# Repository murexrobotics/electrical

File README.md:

# MUREX Electrical

Attempt the impossible.

## Welcome!

Welcome to MUREX Robotics Electrical. We are focused on pushing boundaries and making electronics/systems design more accessible to all.

## Introduction

> *"I do not think there is any thrill that can go through the human heart like that felt by the inventor as he sees some creation of the brain unfolding to success"*
– [Nikola Tesla](https://en.wikipedia.org/wiki/Nikola_Tesla)

MUREX Robotics Electrical focuses on making everything highly integrated and custom. We make industrial/commercial level motion, power, communication, vision and wireless systems accessible to all. By making components fully custom, we can accomplish unprecedented levels of integration within MUREX robotics systems. By keeping COTS parts to a minimum, we vertically integrate all aspects of the robot, minimize space, and surprisingly, minimize cost. We don't do it the easy way. That's not what we believe in.

## Attempt the Impossible

Going to back our "mission statement"... (it's not really a mission statement, more a motivational quote)

> *Attempt the impossible*

What does this mean? Now that you have read through what MUREX Robotics Electrical (or *elec*) is all about and equipped with technical expertise, we can finally say what the true meaning is.

***Attempt the impossible***: We do it the best way possible. If pre-built parts or breakout boards don't cut it, we don't use it. If a processor isn't powerful enough, we don't use it. If a board isn't small enough, we make it smaller. No matter how difficult it may be to accomplish, we will follow through. No matter how hard it is. Things don't always go your way. No matter how hard you try to perfect your schematic, your PCB layout, your system integration, it still might not work out. Things are bound to go wrong, and it is up to *us* do it right. It's "impossible", a non-MUREX Robotics Electrical member might say. However, we accept it as the process. In the end, we will have achieved something others might have called "impossible". But the achievement only comes through endless, motivated attempts at the impossible.

> *Think Different*\
> *Unleash Innovation*\
> *Do It Right*

*Always attempting the impossible,*\
Members:

- Max Liu '26 (@xamuil2)
- Crane Lee '27 (@Crane-Lee)
- Osbert Chang '27 (@Osbertchang)
- Andrew Chen '28

Emeriti:

- Byran Huang '25 (@Hello9999901)
- Altan Unver '25 (@L0ad1n6)
- Varit Asavathiratham '25 (@BaritoDespacito)
- Chaney Hollis '23 (@chaneyhollis)

> December 2023 progress poster

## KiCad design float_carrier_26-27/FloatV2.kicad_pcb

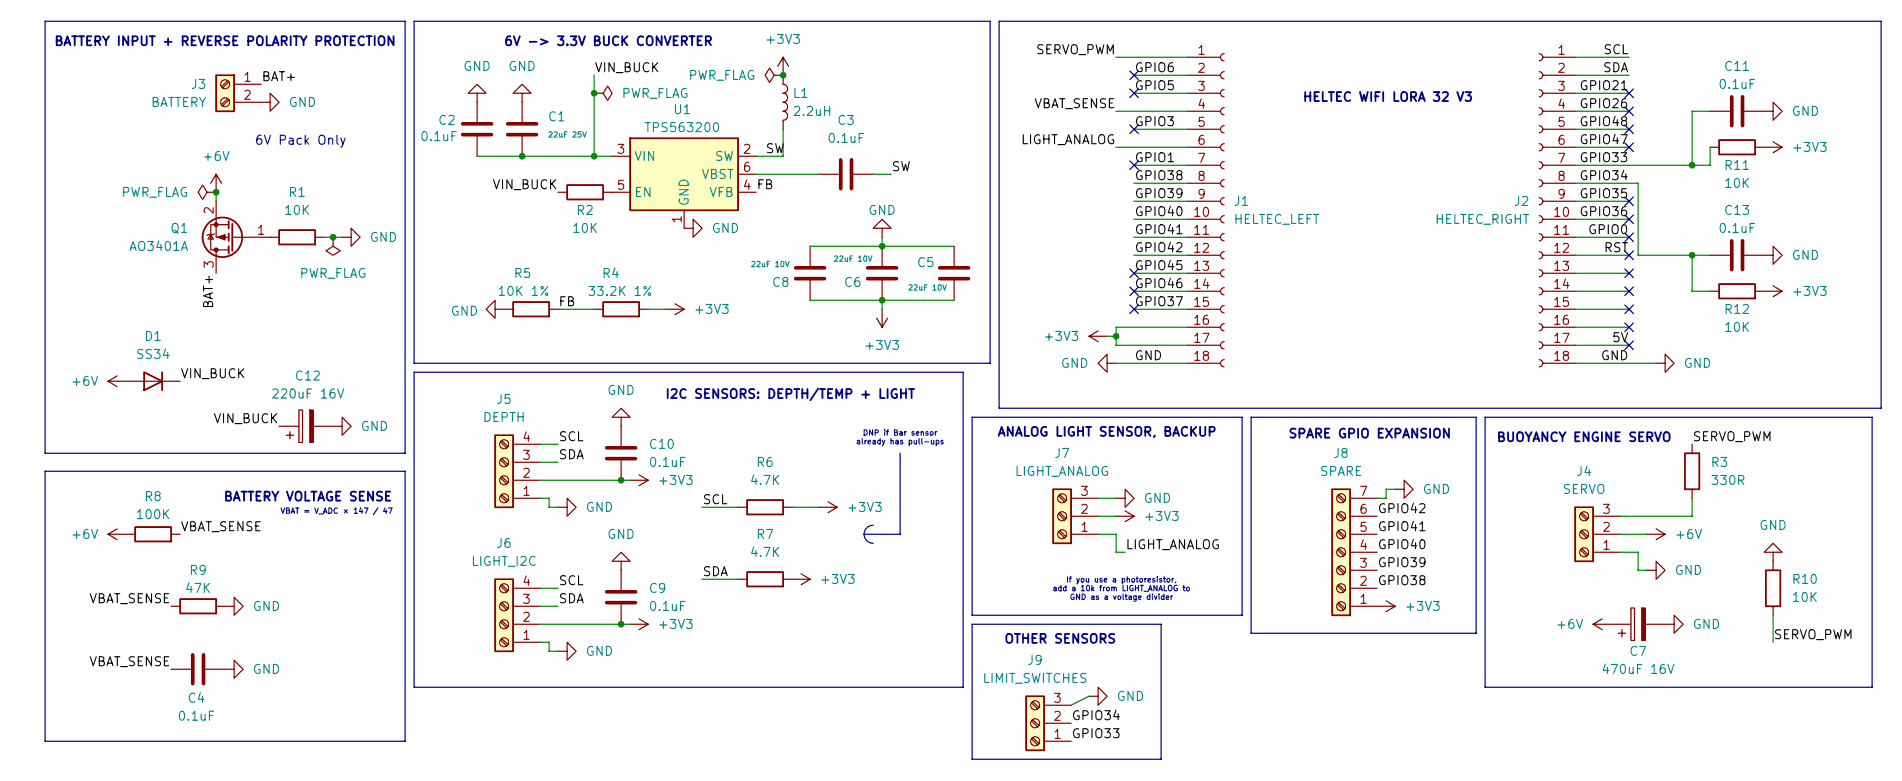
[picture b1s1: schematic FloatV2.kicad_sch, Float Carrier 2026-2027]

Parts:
C1: 22uF 25V; C_1206_3216Metric
C2, C3, C4, C9, C10, C11, C13: 0.1uF; C_0603_1608Metric
C5, C6, C8: 22uF 10V; C_0805_2012Metric
C7: 470uF 16V; CP_Elec_8x10
C12: 220uF 16V; CP_Elec_8x10
D1: SS34; D_SMA
J1: HELTEC_LEFT; PinSocket_1x18_P2.54mm_Vertical
J2: HELTEC_RIGHT; PinSocket_1x18_P2.54mm_Vertical
J3: BATTERY; TerminalBlock_Xinya_XY308-2.54-2P_1x02_P2.54mm_Horizontal
J4: SERVO; TerminalBlock_Xinya_XY308-2.54-3P_1x03_P2.54mm_Horizontal
J5: DEPTH; TerminalBlock_Xinya_XY308-2.54-4P_1x04_P2.54mm_Horizontal
J6: LIGHT_I2C; TerminalBlock_Xinya_XY308-2.54-4P_1x04_P2.54mm_Horizontal
J7: LIGHT_ANALOG; TerminalBlock_Xinya_XY308-2.54-3P_1x03_P2.54mm_Horizontal
J8: SPARE; TerminalBlock_Xinya_XY308-2.54-7P_1x07_P2.54mm_Horizontal
J9: LIMIT_SWITCHES; TerminalBlock_Xinya_XY308-2.54-3P_1x03_P2.54mm_Horizontal
L1: 2.2uH; L_Bourns_SRP7028A_7.3x6.6mm
Q1: AO3401A; SOT-23
R1, R2, R10, R11, R12: 10K; R_0603_1608Metric
R3: 330R; R_0603_1608Metric
R4: 33.2K 1%; R_0603_1608Metric
R5: 10K 1%; R_0603_1608Metric
R6, R7: 4.7K; R_0603_1608Metric
R8: 100K; R_0603_1608Metric
R9: 47K; R_0603_1608Metric
U1: TPS563200; SOT-23-6

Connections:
+3V3: C5.2, C6.1, C8.1, C9.2, C10.2, J1.16, J1.17, J5.2, J6.2, J7.2, J8.1, L1.1, R4.2, R6.2, R7.2, R11.2, R12.2
+6V: C7.1, D1.2 (A), J4.2, Q1.2 (S), R8.1
/5V: J2.17
/BAT+: J3.1, Q1.3 (D)
/FB: R4.1, R5.2, U1.4 (VFB)
/GPIO0: J2.11
/GPIO1: J1.7
/GPIO3: J1.5
/GPIO5: J1.3
/GPIO6: J1.2
/GPIO21: J2.3
/GPIO26: J2.4
/GPIO33: C11.1, J2.7, J9.1, R11.1
/GPIO34: C13.1, J2.8, J9.2, R12.1
/GPIO35: J2.9
/GPIO36: J2.10
/GPIO37: J1.15
/GPIO38: J1.8, J8.2
/GPIO39: J1.9, J8.3
/GPIO40: J1.10, J8.4
/GPIO41: J1.11, J8.5
/GPIO42: J1.12, J8.6
/GPIO45: J1.13
/GPIO46: J1.14
/GPIO47: J2.6
/GPIO48: J2.5
/LIGHT_ANALOG: J1.6, J7.1
/RST: J2.12
/SCL: J2.1, J5.4, J6.4, R6.1
/SDA: J2.2, J5.3, J6.3, R7.1
/SERVO_PWM: J1.1, R3.1, R10.2
/SW: C3.1, L1.2, U1.2 (SW)
/VBAT_SENSE: C4.2, J1.4, R8.2, R9.1
/VIN_BUCK: C1.2, C2.2, C12.1, D1.1 (K), R2.1, U1.3 (VIN)
GND: C1.1, C2.1, C4.1, C5.1, C6.2, C7.2, C8.2, C9.1, C10.1, C11.2, C12.2, C13.2, J1.18, J2.18, J3.2, J4.1, J5.1, J6.1, J7.3, J8.7, J9.3, R1.2, R5.1, R9.2, R10.1, U1.1 (GND)
unnamed: J4.3, R3.2
unnamed: Q1.1 (G), R1.1
unnamed: R2.2, U1.5 (EN)
unnamed: C3.2, U1.6 (VBST)

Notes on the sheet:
I2C SENSORS: DEPTH/TEMP + LIGHT
BATTERY INPUT + REVERSE POLARITY PROTECTION
6V Pack Only
SPARE GPIO EXPANSION
6V -> 3.3V BUCK CONVERTER
VBAT = V_ADC × 147 / 47
DNP if Bar sensor already has pull-ups
HELTEC WIFI LORA 32 V3
ANALOG LIGHT SENSOR, BACKUP
If you use a photoresistor, add a 10k from LIGHT_ANALOG to GND as a voltage divider
BATTERY VOLTAGE SENSE
OTHER SENSORS
BUOYANCY ENGINE SERVO

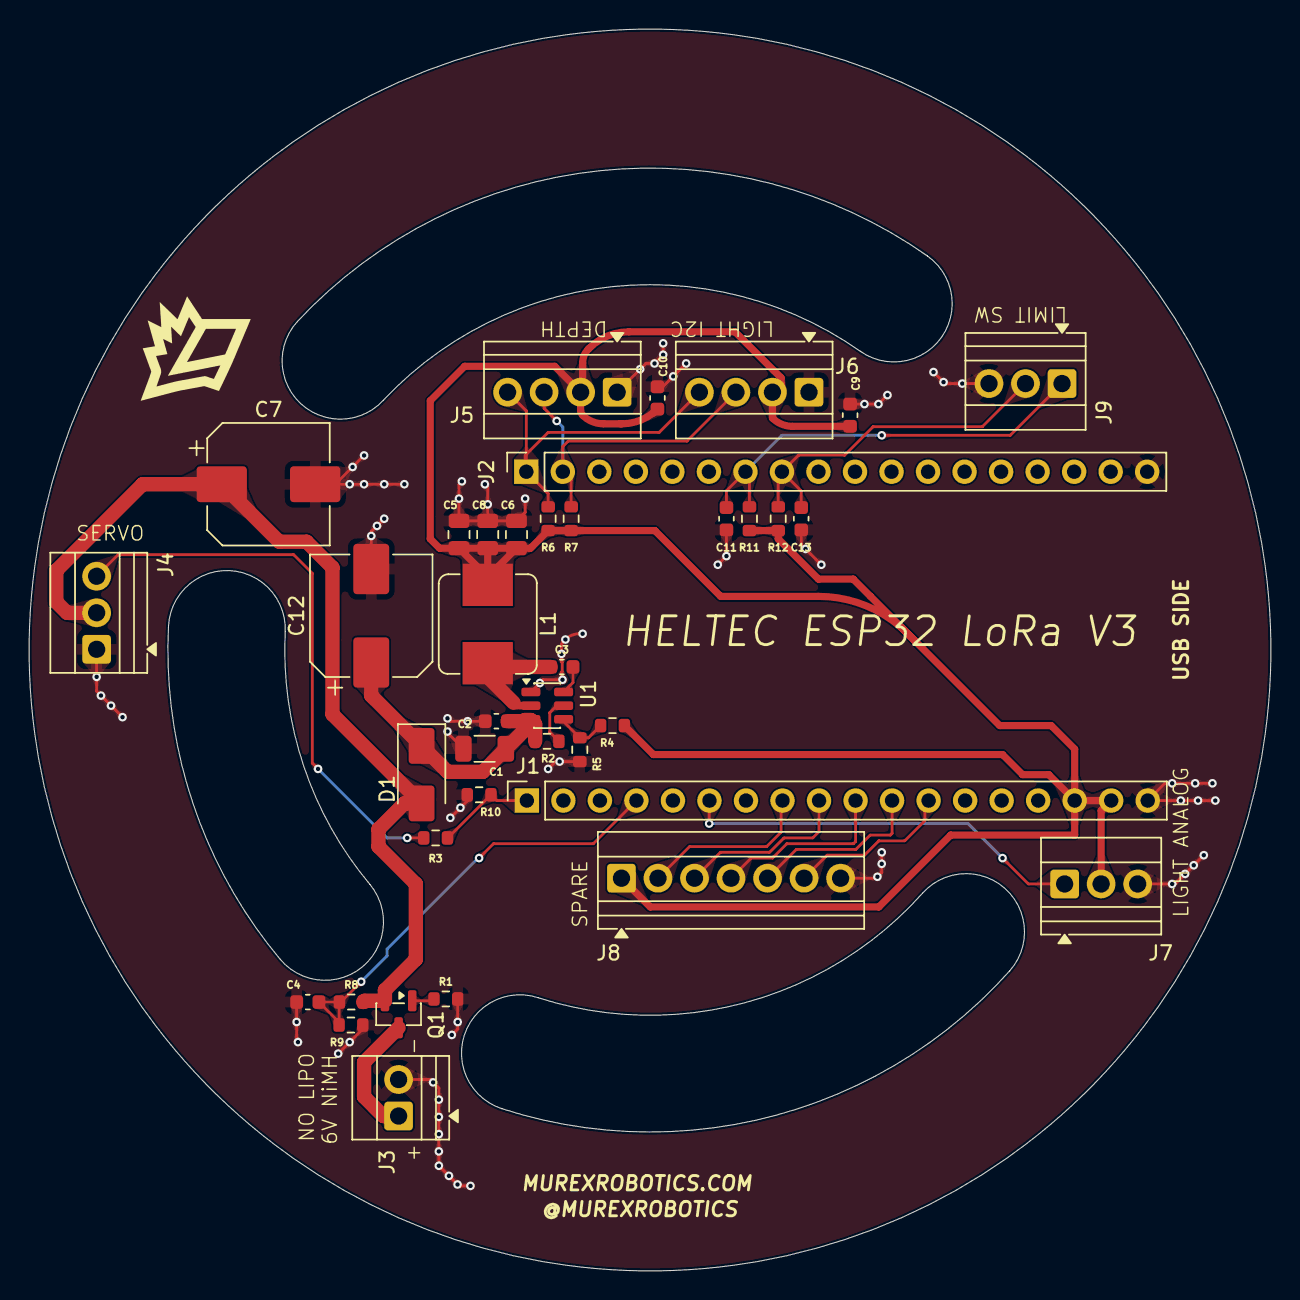
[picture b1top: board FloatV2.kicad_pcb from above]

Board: 4 copper layers, 86.4 x 86.4 mm, 38 parts (0 on the bottom side), 23 nets.

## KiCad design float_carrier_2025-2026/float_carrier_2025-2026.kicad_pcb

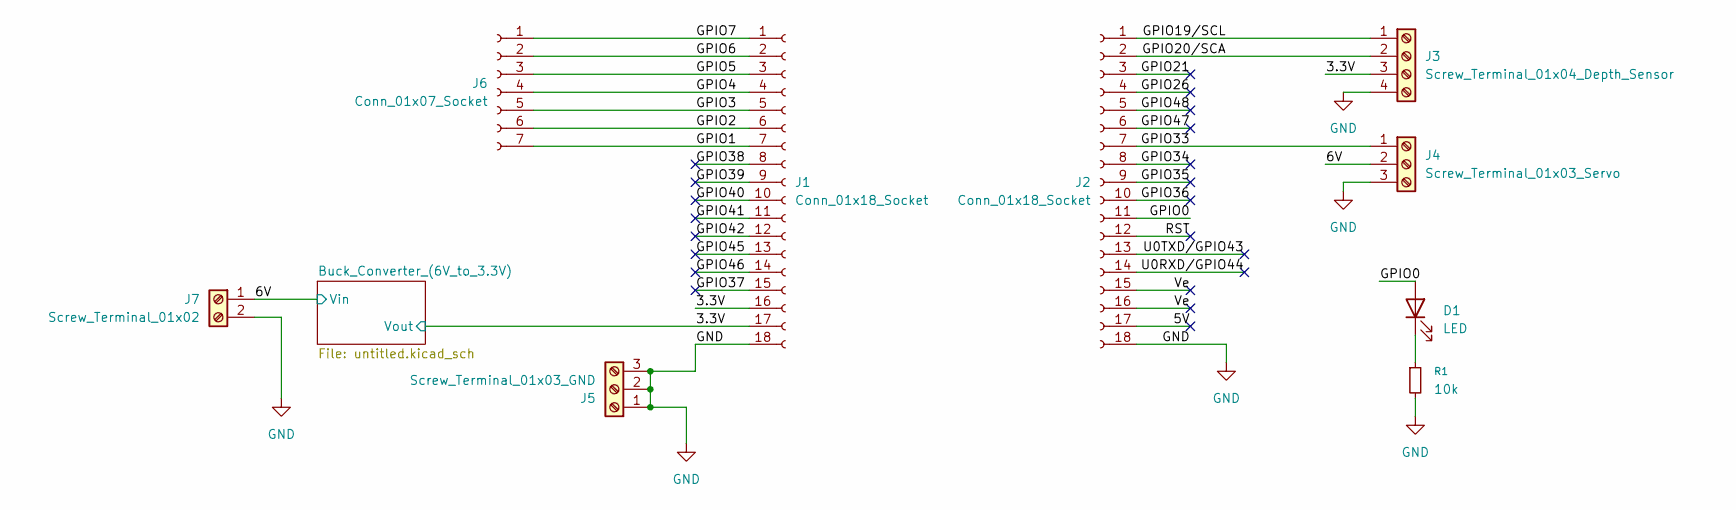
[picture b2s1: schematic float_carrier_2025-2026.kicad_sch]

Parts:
D1: LED; LED_0603_1608Metric
J1, J2: Conn_01x18_Socket; PinSocket_1x18_P2.54mm_Vertical
J3: Screw_Terminal_01x04_Depth_Sensor; TerminalBlock_Xinya_XY308-2.54-4P_1x04_P2.54mm_Horizontal
J4: Screw_Terminal_01x03_Servo; TerminalBlock_Xinya_XY308-2.54-3P_1x03_P2.54mm_Horizontal
J5: Screw_Terminal_01x03_GND; TerminalBlock_Xinya_XY308-2.54-3P_1x03_P2.54mm_Horizontal
J6: Conn_01x07_Socket; PinSocket_1x07_P2.54mm_Vertical
J7: Screw_Terminal_01x02; TerminalBlock_Xinya_XY308-2.54-2P_1x02_P2.54mm_Horizontal
R1: 10k; R_0603_1608Metric

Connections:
/3.3V: J1.16, J1.17, J3.3; also elsewhere on the board
/5V: J2.17
/6V: J4.2, J7.1; also elsewhere on the board
/GPIO0: D1.2 (A), J2.11
/GPIO1: J1.7, J6.7
/GPIO2: J1.6, J6.6
/GPIO3: J1.5, J6.5
/GPIO4: J1.4, J6.4
/GPIO5: J1.3, J6.3
/GPIO6: J1.2, J6.2
/GPIO7: J1.1, J6.1
/GPIO19/SCL: J2.1, J3.1
/GPIO20/SCA: J2.2, J3.2
/GPIO21: J2.3
/GPIO26: J2.4
/GPIO33: J2.7, J4.1
/GPIO34: J2.8
/GPIO35: J2.9
/GPIO36: J2.10
/GPIO37: J1.15
/GPIO38: J1.8
/GPIO39: J1.9
/GPIO40: J1.10
/GPIO41: J1.11
/GPIO42: J1.12
/GPIO45: J1.13
/GPIO46: J1.14
/GPIO47: J2.6
/GPIO48: J2.5
/RST: J2.12
/U0RXD/GPIO44: J2.14
/U0TXD/GPIO43: J2.13
/Ve: J2.15, J2.16
GND: J1.18, J2.18, J3.4, J4.3, J5.1, J5.2, J5.3, J7.2, R1.2; also elsewhere on the board
unnamed: D1.1 (K), R1.1

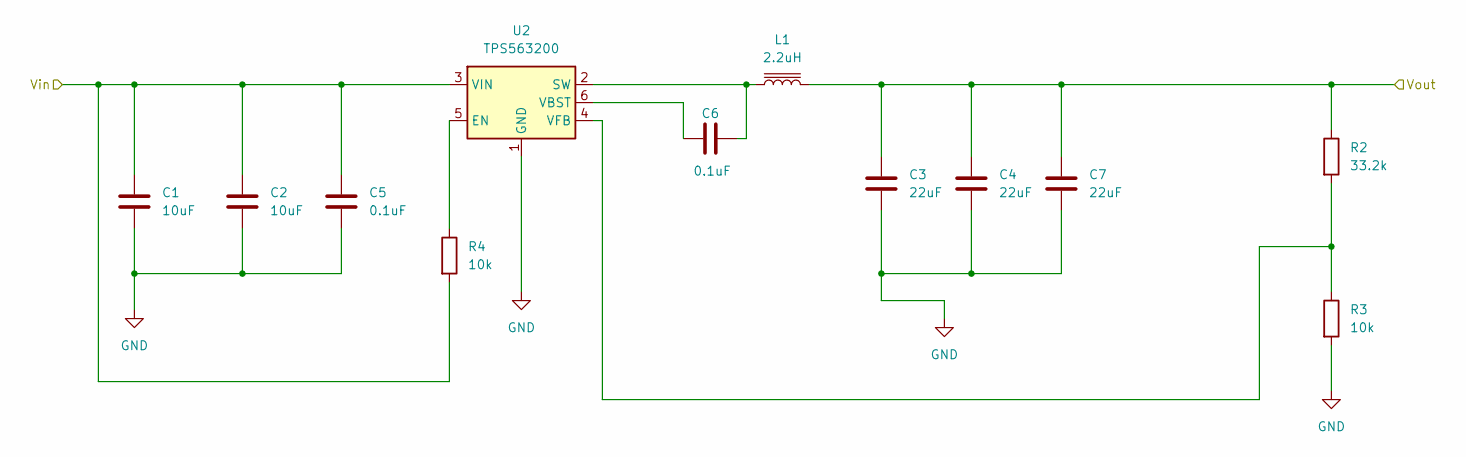
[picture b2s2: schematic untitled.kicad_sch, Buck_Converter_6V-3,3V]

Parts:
C1, C2: 10uF; C_0603_1608Metric
C3, C4, C7: 22uF; C_0603_1608Metric
C5, C6: 0.1uF; C_0402_1005Metric
L1: 2.2uH; L_Bourns_SRP7028A_7.3x6.6mm
R2: 33.2k; R_0603_1608Metric
R3, R4: 10k; R_0603_1608Metric
U2: TPS563200; SOT-23-6

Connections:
/3.3V: C3.1, C4.1, C7.1, L1.2, R2.1; also elsewhere on the board
/6V: C1.1, C2.1, C5.1, R4.2, U2.3 (VIN); also elsewhere on the board
GND: C1.2, C2.2, C3.2, C4.2, C5.2, C7.2, R3.2, U2.1 (GND); also elsewhere on the board
unnamed: R4.1, U2.5 (EN)
unnamed: C6.2, L1.1, U2.2 (SW)
unnamed: C6.1, U2.6 (VBST)
unnamed: R2.2, R3.1, U2.4 (VFB)

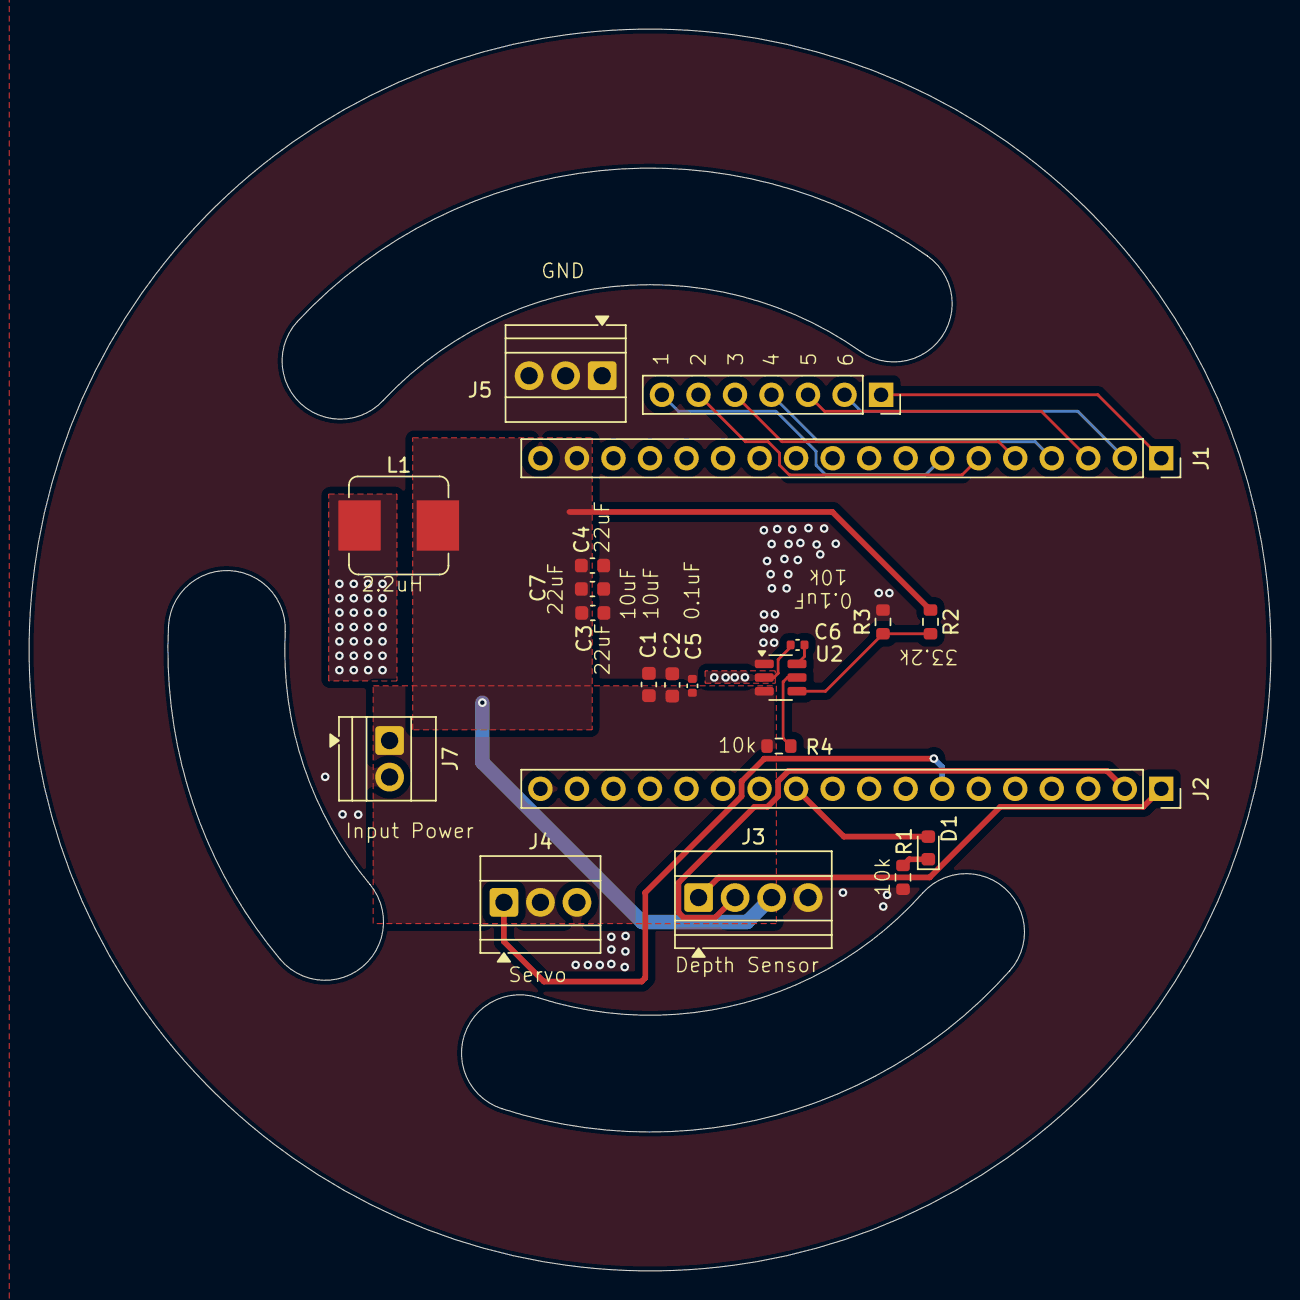
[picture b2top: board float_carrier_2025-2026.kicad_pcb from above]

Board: 2 copper layers, 86.4 x 86.4 mm, 21 parts (0 on the bottom side), 20 nets.

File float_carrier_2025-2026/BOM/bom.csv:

Comment,Designator,Footprint,LSCS Part Number
0.1uF,"C5, C6",C_0402_1005Metric,C141382
10uF,"C1, C2",C_0603_1608Metric,C694533
22uF,"C3, C4, C7",C_0603_1608Metric,C60077
LED,D1,LED_0603_1608Metric,C2286
2.2uH,L1,L_Bourns_SRP7028A_7.3x6.6mm,C2847539
10k,"R1, R3, R4",R_0603_1608Metric,C5123581
33.2k,R2,R_0603_1608Metric,C23003
TPS563200,U2,SOT-23-6,C97253

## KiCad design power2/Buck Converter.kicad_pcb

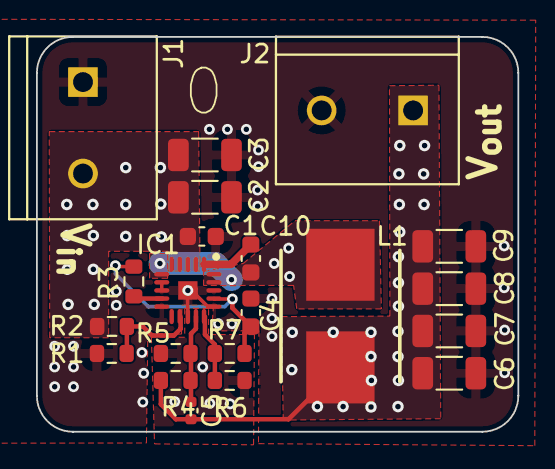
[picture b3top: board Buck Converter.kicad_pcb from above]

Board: 4 copper layers, 26.7 x 21.9 mm, 21 parts (0 on the bottom side), 10 nets.

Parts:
C1, C10: 0.1uF; C_0603_1608Metric
C2, C3: 22uF; C_1206_3216Metric
C4: 1uF; C_0603_1608Metric
C5: 68pF; C_0402_1005Metric
C6, C7, C8, C9: 47uF; C_1206_3216Metric
IC1: TPS56C230RJER; QFN45P300X300X100-21N-D
J1, J2: TE_282837-2
L1: SRP7028A-1R8M; INDPM7366X300N
R1: 51k; R_0603_1608Metric
R2: 102k; R_0603_1608Metric
R3: 100k; R_0603_1608Metric
R4: 110k; R_0603_1608Metric
R5, R6: 15k; R_0603_1608Metric
R7: 330k; R_0603_1608Metric

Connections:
/EN: IC1.12 (EN), R1.1, R2.2
/MODE: IC1.15 (MODE), R6.1, R7.1
/V_{IN}: C1.2, C2.2, C3.2, IC1.2 (VIN_1), IC1.3 (VIN_2), IC1.4 (VIN_3), IC1.5 (VIN_4), J1.2, R2.1
/V_{OUT}: C5.2, C6.1, C7.1, C8.1, C9.1, J2.1, L1.2, R4.1
GND: C1.1, C2.1, C3.1, C4.2, C6.2, C7.2, C8.2, C9.2, IC1.7 (PGND_1), IC1.8 (PGND_2), IC1.10 (NC_1), IC1.13 (AGND), IC1.16 (NC_2), IC1.18 (PGND_3), IC1.21 (PGND_4), J1.1, J2.2, R1.2, R5.2, R6.2
unnamed: C10.1, IC1.1 (BST)
unnamed: C5.1, IC1.14 (FB), R4.2, R5.1
unnamed: IC1.9 (PGOOD), R3.2
unnamed: C10.2, IC1.6 (SW_1), IC1.19 (SW_2), IC1.20 (SW_3), L1.1
unnamed: C4.1, IC1.17 (VCC), R3.1, R7.2

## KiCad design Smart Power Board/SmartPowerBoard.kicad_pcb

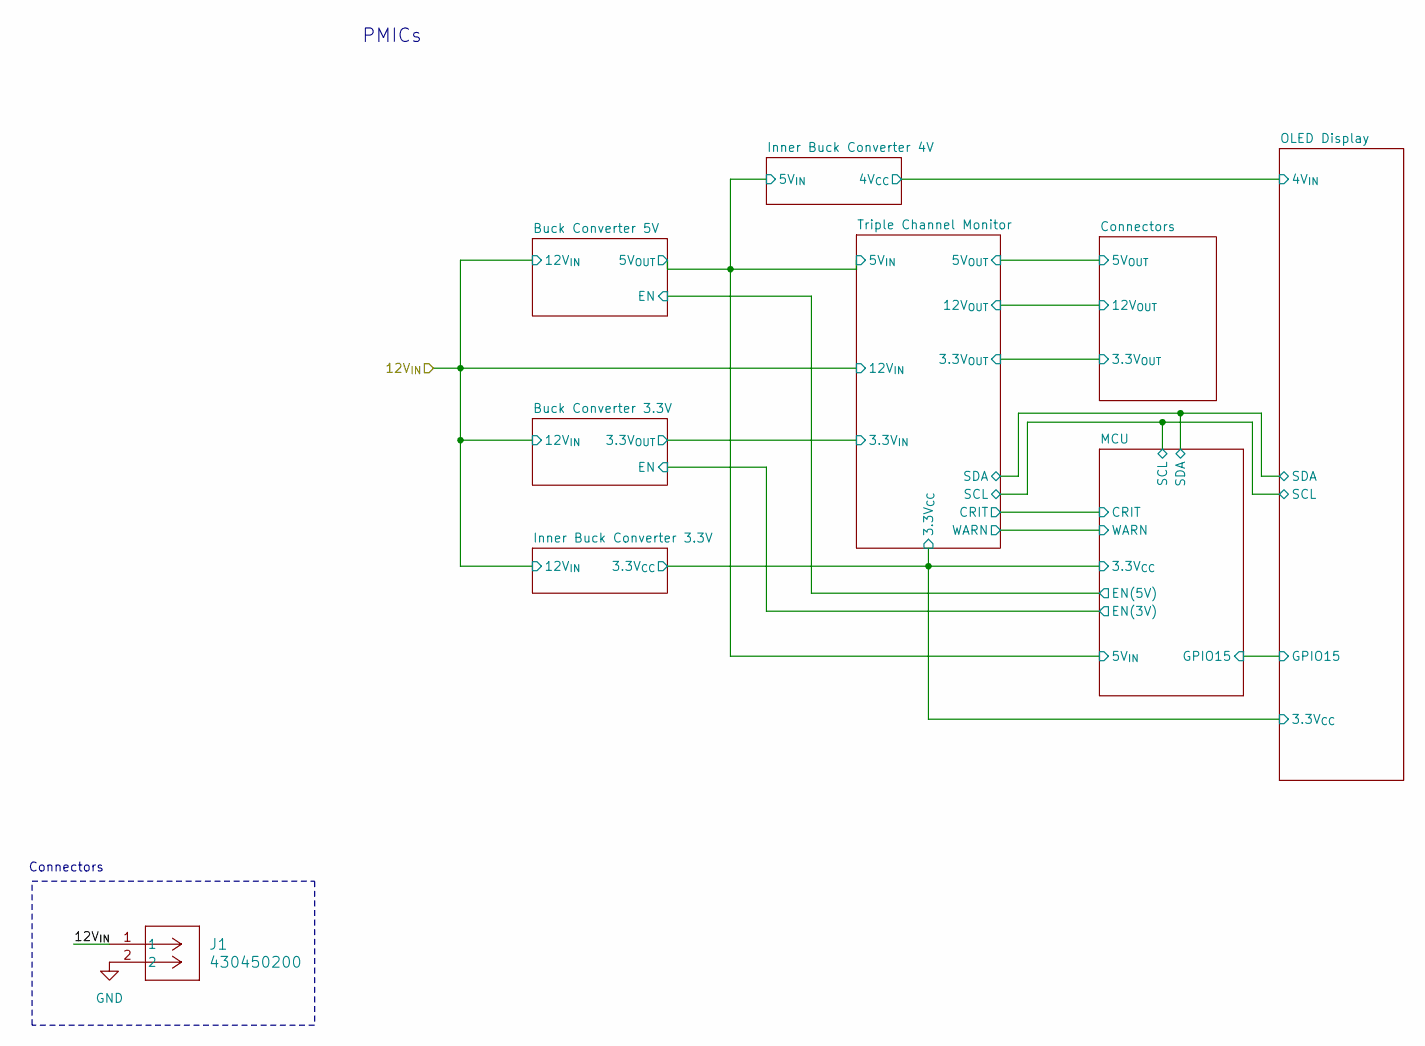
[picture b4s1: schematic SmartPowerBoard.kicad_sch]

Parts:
J1: 430450200; CON_430450200_MOL

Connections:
/12V_{IN}: J1.1; also elsewhere on the board
GND: J1.2; also elsewhere on the board

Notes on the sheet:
Connectors
PMICs

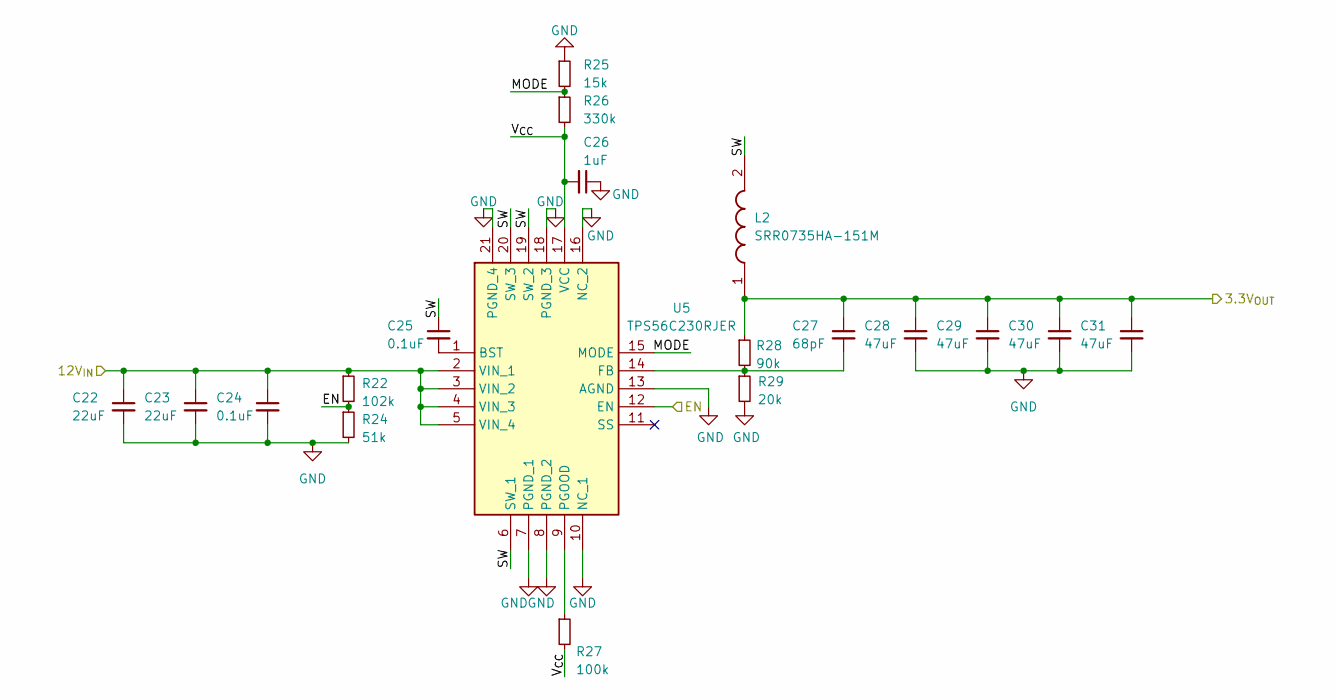
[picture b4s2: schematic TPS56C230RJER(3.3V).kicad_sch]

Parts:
C22, C23: 22uF; C_0603_1608Metric
C24, C25: 0.1uF; C_0402_1005Metric
C26: 1uF; C_0402_1005Metric
C27: 68pF; C_0201_0603Metric
C28, C29, C30, C31: 47uF; C_0603_1608Metric
L2: SRR0735HA-151M; SRR0735HA151M; Mouser Part Number 652-SRR0735HA-151M
R22: 102k; R_0402_1005Metric
R24: 51k; R_0402_1005Metric
R25: 15k; R_0402_1005Metric
R26: 330k; R_0402_1005Metric
R27: 100k; R_0402_1005Metric
R28: 90k; R_0402_1005Metric
R29: 20k; R_0402_1005Metric
U5: TPS56C230RJER; QFN45P300X300X100-21N-D; Manufacturer_Part_Number TPS56C230RJER; Mouser Part Number 595-TPS56C230RJER

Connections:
/12V_{IN}: C22.1, C23.1, C24.1, R22.1, U5.2 (VIN_1), U5.3 (VIN_2), U5.4 (VIN_3), U5.5 (VIN_4); also elsewhere on the board
/Buck Converter 3.3V/3.3V_{OUT}: C27.1, C28.1, C29.1, C30.1, C31.1, L2.1, R28.1; also elsewhere on the board
/Buck Converter 3.3V/EN: R22.2, R24.1, U5.12 (EN); also elsewhere on the board
/Buck Converter 3.3V/MODE: R25.2, R26.1, U5.15 (MODE)
/Buck Converter 3.3V/SW: C25.1, L2.2, U5.6 (SW_1), U5.19 (SW_2), U5.20 (SW_3)
/Buck Converter 3.3V/V_{CC}: C26.2, R26.2, R27.2, U5.17 (VCC)
GND: C22.2, C23.2, C24.2, C26.1, C28.2, C29.2, C30.2, C31.2, R24.2, R25.1, R29.2, U5.7 (PGND_1), U5.8 (PGND_2), U5.10 (NC_1), U5.13 (AGND), U5.16 (NC_2), U5.18 (PGND_3), U5.21 (PGND_4); also elsewhere on the board
unnamed: C25.2, U5.1 (BST)
unnamed: C27.2, R28.2, R29.1, U5.14 (FB)
unnamed: R27.1, U5.9 (PGOOD)

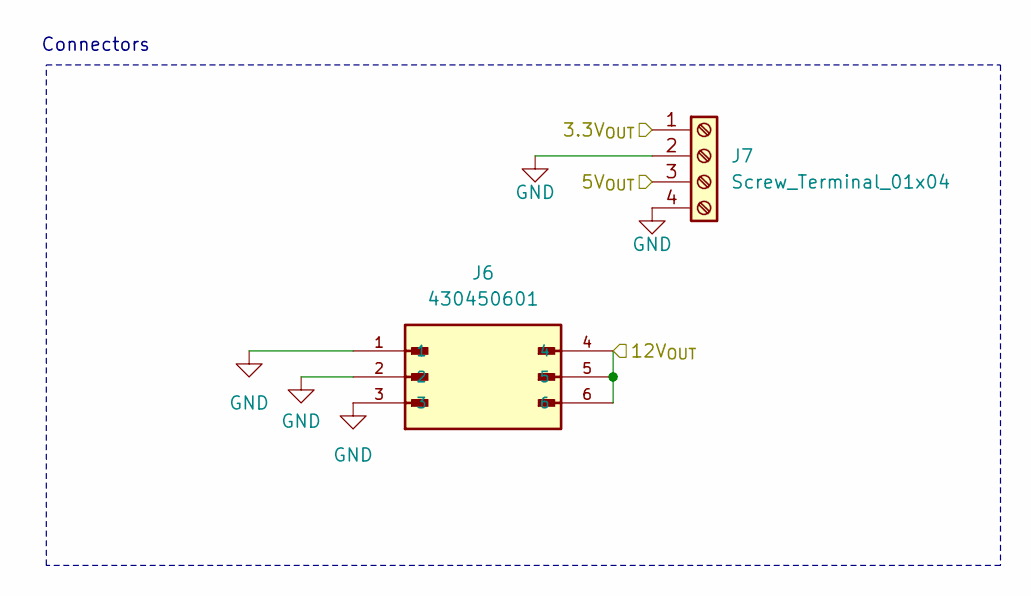
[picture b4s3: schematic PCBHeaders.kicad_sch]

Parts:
J6: 430450601; MOLEX_430450601; PARTREV G
J7: Screw_Terminal_01x04; 2828574

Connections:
/Connectors/3.3V_{OUT}: J7.1; also elsewhere on the board
/Connectors/5V_{OUT}: J7.3; also elsewhere on the board
/Connectors/12V_{OUT}: J6.4, J6.5, J6.6; also elsewhere on the board
GND: J6.1, J6.2, J6.3, J7.2, J7.4; also elsewhere on the board

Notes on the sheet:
Connectors

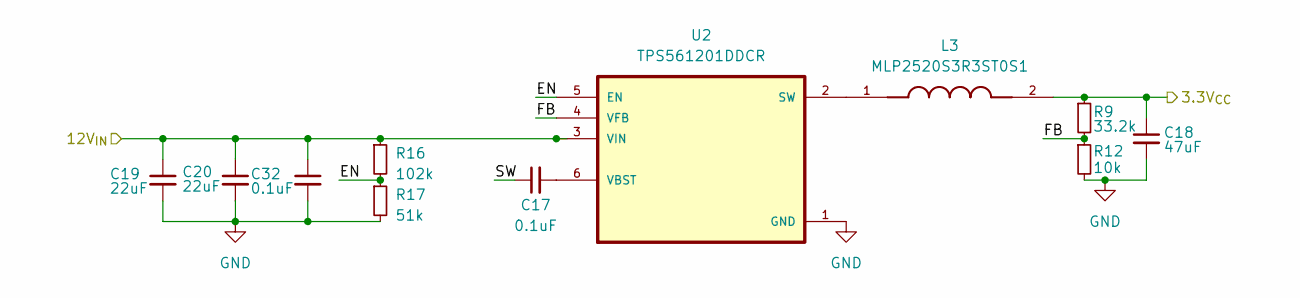
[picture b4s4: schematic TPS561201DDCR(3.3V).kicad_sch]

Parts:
C17, C32: 0.1uF; C_0402_1005Metric
C18: 47uF; C_0603_1608Metric
C19, C20: 22uF; C_0603_1608Metric
L3: MLP2520S3R3ST0S1; INDC2520X120N
R9: 33.2k; R_0402_1005Metric
R12: 10k; R_0402_1005Metric
R16: 102k; R_0402_1005Metric
R17: 51k; R_0402_1005Metric
U2: TPS561201DDCR; SOT95P280X110-6N

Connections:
/12V_{IN}: C19.1, C20.1, C32.1, R16.1, U2.3 (VIN); also elsewhere on the board
/Inner Buck Converter 3.3V/EN: R16.2, R17.1, U2.5 (EN)
/Inner Buck Converter 3.3V/FB: R9.2, R12.1, U2.4 (VFB)
/Inner Buck Converter 3.3V/SW: C17.1
/MCU/3.3V_{CC}: C18.1, L3.2, R9.1; also elsewhere on the board
GND: C18.2, C19.2, C20.2, C32.2, R12.2, R17.2, U2.1 (GND); also elsewhere on the board
unnamed: L3.1, U2.2 (SW)
unnamed: C17.2, U2.6 (VBST)

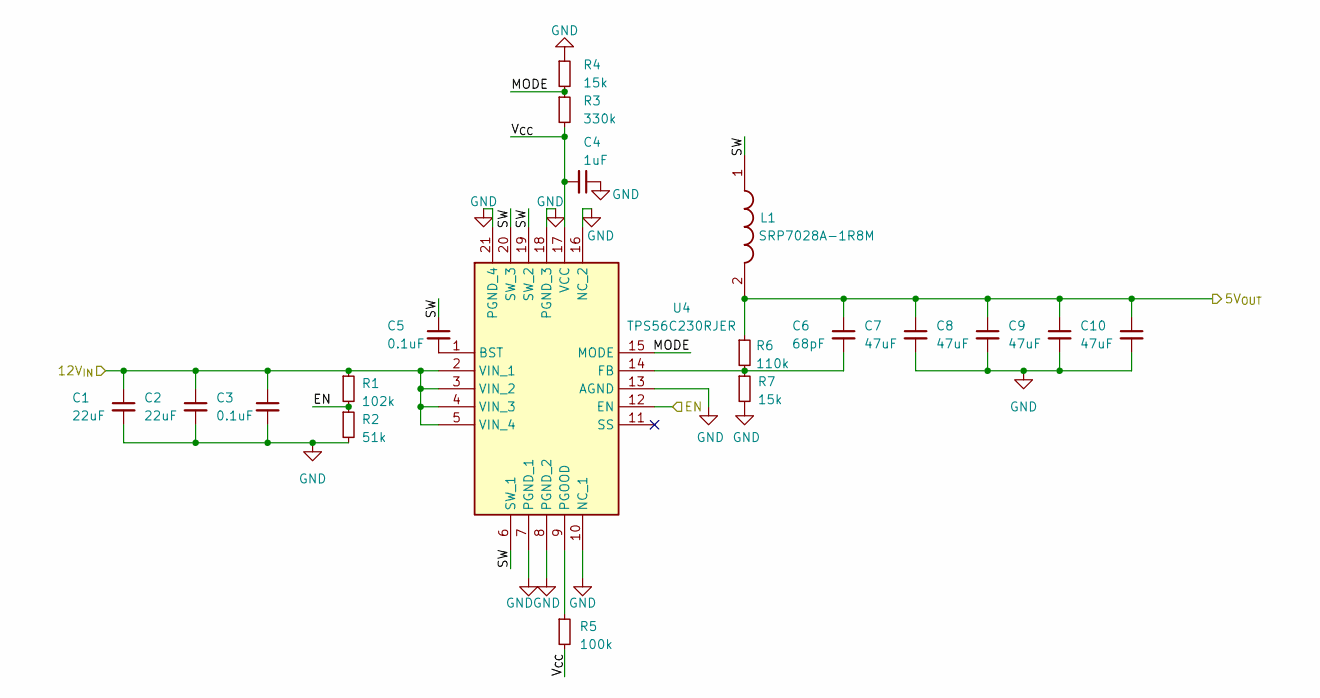
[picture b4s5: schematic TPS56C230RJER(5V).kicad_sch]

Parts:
C1, C2: 22uF; C_0603_1608Metric
C3, C5: 0.1uF; C_0402_1005Metric
C4: 1uF; C_0402_1005Metric
C6: 68pF; C_0201_0603Metric
C7, C8, C9, C10: 47uF; C_0603_1608Metric
L1: SRP7028A-1R8M; INDPM7366X300N; Manufacturer_Part_Number SRP7028A-1R8M; Mouser Part Number 652-SRP7028A-1R8M
R1: 102k; R_0402_1005Metric
R2: 51k; R_0402_1005Metric
R3: 330k; R_0402_1005Metric
R4, R7: 15k; R_0402_1005Metric
R5: 100k; R_0402_1005Metric
R6: 110k; R_0402_1005Metric
U4: TPS56C230RJER; QFN45P300X300X100-21N-D; Manufacturer_Part_Number TPS56C230RJER; Mouser Part Number 595-TPS56C230RJER

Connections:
/12V_{IN}: C1.1, C2.1, C3.1, R1.1, U4.2 (VIN_1), U4.3 (VIN_2), U4.4 (VIN_3), U4.5 (VIN_4); also elsewhere on the board
/Buck Converter 5V/5V_{OUT}: C6.1, C7.1, C8.1, C9.1, C10.1, L1.2, R6.1; also elsewhere on the board
/Buck Converter 5V/EN: R1.2, R2.1, U4.12 (EN); also elsewhere on the board
/Buck Converter 5V/MODE: R3.1, R4.2, U4.15 (MODE)
/Buck Converter 5V/SW: C5.1, L1.1, U4.6 (SW_1), U4.19 (SW_2), U4.20 (SW_3)
/Buck Converter 5V/V_{CC}: C4.2, R3.2, R5.2, U4.17 (VCC)
GND: C1.2, C2.2, C3.2, C4.1, C7.2, C8.2, C9.2, C10.2, R2.2, R4.1, R7.2, U4.7 (PGND_1), U4.8 (PGND_2), U4.10 (NC_1), U4.13 (AGND), U4.16 (NC_2), U4.18 (PGND_3), U4.21 (PGND_4); also elsewhere on the board
unnamed: C5.2, U4.1 (BST)
unnamed: C6.2, R6.2, R7.1, U4.14 (FB)
unnamed: R5.1, U4.9 (PGOOD)

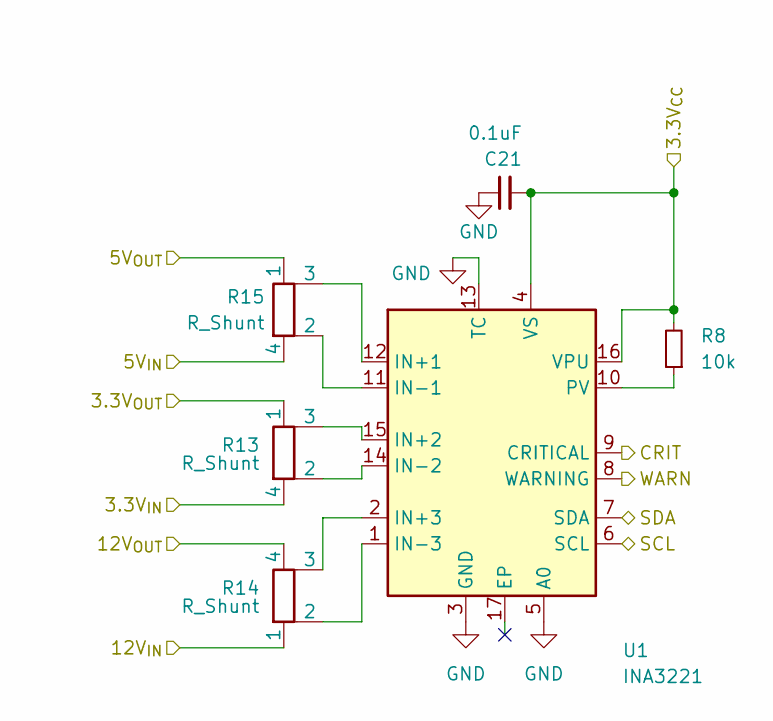
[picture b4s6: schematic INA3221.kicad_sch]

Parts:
C21: 0.1uF; C_0402_1005Metric
R8: 10k; C_0402_1005Metric
R13, R15: R_Shunt; R_Shunt_Ohmite_LVK12
R14: R_Shunt; R_Shunt_Ohmite_LVK20
U1: INA3221; Texas_RGV0016A_VQFN-16-1EP_4x4mm_P0.65mm_EP2.1x2.1mm

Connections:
/12V_{IN}: R14.1; also elsewhere on the board
/Buck Converter 3.3V/3.3V_{OUT}: R13.4; also elsewhere on the board
/Buck Converter 5V/5V_{OUT}: R15.4; also elsewhere on the board
/Connectors/3.3V_{OUT}: R13.1; also elsewhere on the board
/Connectors/5V_{OUT}: R15.1; also elsewhere on the board
/Connectors/12V_{OUT}: R14.4; also elsewhere on the board
/MCU/3.3V_{CC}: C21.2, R8.2, U1.4 (VS), U1.16 (VPU); also elsewhere on the board
/MCU/CRIT: U1.9 (CRITICAL); also elsewhere on the board
/MCU/SCL: U1.6 (SCL); also elsewhere on the board
/MCU/SDA: U1.7 (SDA); also elsewhere on the board
/MCU/WARN: U1.8 (WARNING); also elsewhere on the board
GND: C21.1, U1.3 (GND), U1.5 (A0), U1.13 (TC); also elsewhere on the board
unnamed: R15.3, U1.12 (IN+1)
unnamed: R13.3, U1.15 (IN+2)
unnamed: R14.3, U1.2 (IN+3)
unnamed: R15.2, U1.11 (IN-1)
unnamed: R13.2, U1.14 (IN-2)
unnamed: R14.2, U1.1 (IN-3)
unnamed: R8.1, U1.10 (PV)

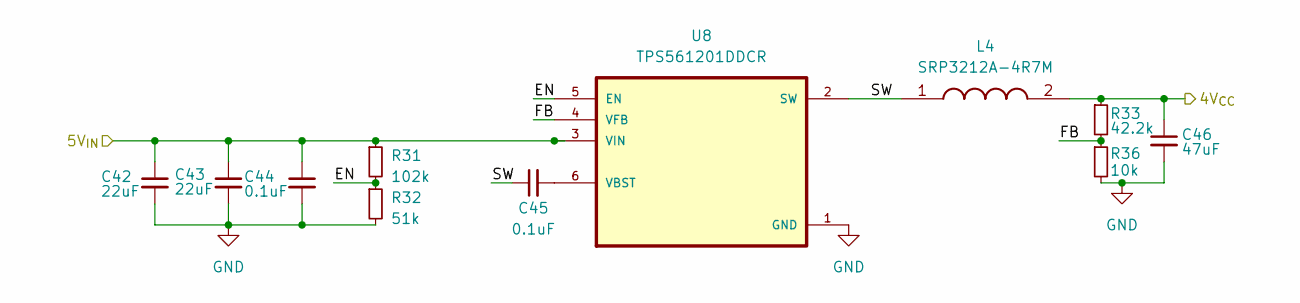
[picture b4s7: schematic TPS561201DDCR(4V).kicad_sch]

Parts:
C42, C43: 22uF; C_0603_1608Metric
C44, C45: 0.1uF; C_0402_1005Metric
C46: 47uF; C_0603_1608Metric
L4: SRP3212A-4R7M; INDC3225X120N; Mouser Part Number 652-SRP3212A-4R7M
R31: 102k; R_0402_1005Metric
R32: 51k; R_0402_1005Metric
R33: 42.2k; R_0402_1005Metric
R36: 10k; R_0402_1005Metric
U8: TPS561201DDCR; SOT95P280X110-6N

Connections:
/Buck Converter 5V/5V_{OUT}: C42.1, C43.1, C44.1, R31.1, U8.3 (VIN); also elsewhere on the board
/Inner Buck Converter 4V/4V_{CC}: C46.1, L4.2, R33.1; also elsewhere on the board
/Inner Buck Converter 4V/EN: R31.2, R32.1, U8.5 (EN)
/Inner Buck Converter 4V/FB: R33.2, R36.1, U8.4 (VFB)
/Inner Buck Converter 4V/SW: C45.1, L4.1, U8.2 (SW)
GND: C42.2, C43.2, C44.2, C46.2, R32.2, R36.2, U8.1 (GND); also elsewhere on the board
unnamed: C45.2, U8.6 (VBST)

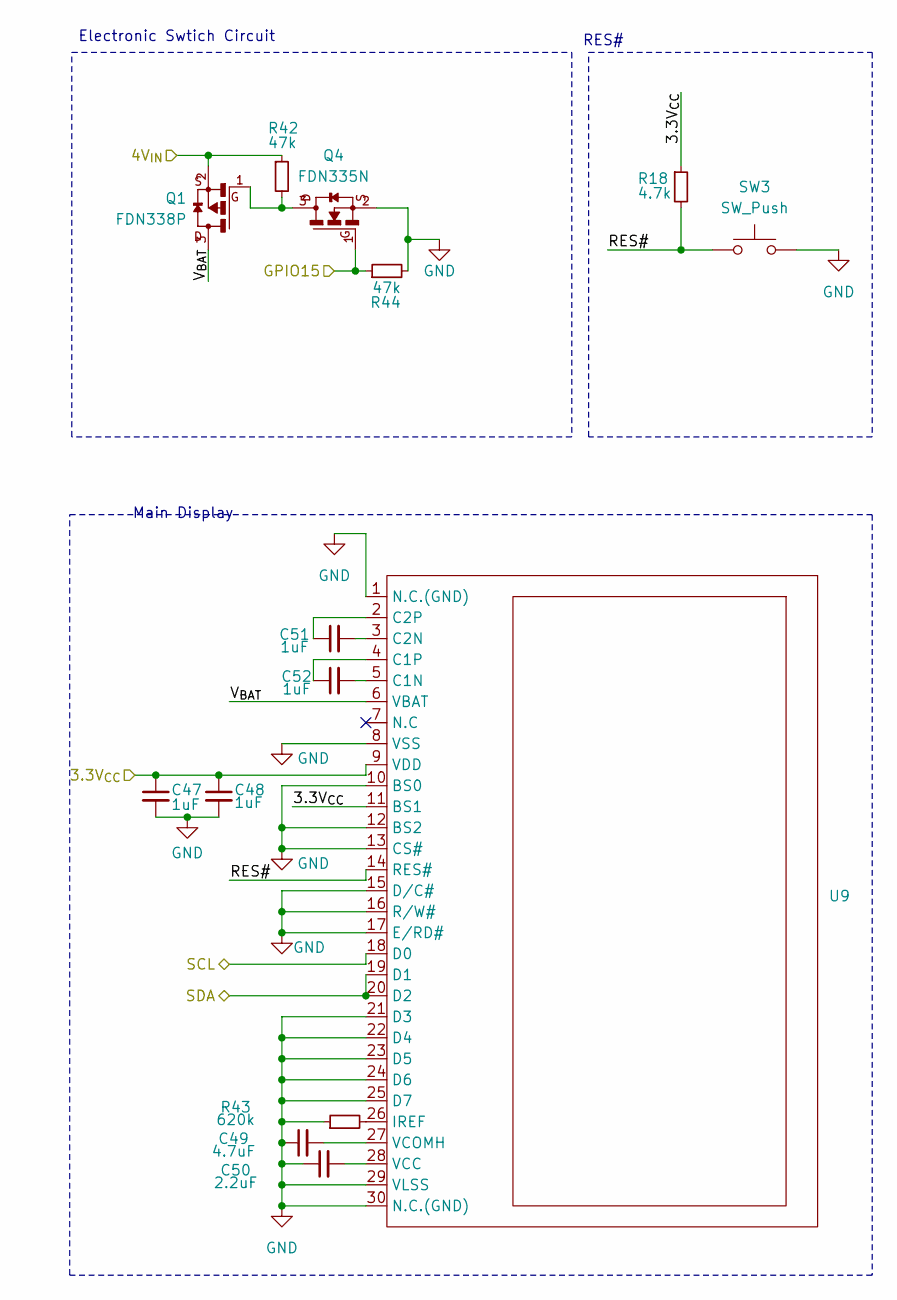
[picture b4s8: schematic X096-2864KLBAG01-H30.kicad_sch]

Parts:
C47, C48, C51, C52: 1uF; C_0402_1005Metric
C49: 4.7uF; C_0402_1005Metric
C50: 2.2uF; C_0402_1005Metric
Q1: FDN338P; SSOT-3
Q4: FDN335N; SSOT-3
R18: 4.7k; R_0402_1005Metric
R42, R44: 47k; R_0402_1005Metric
R43: 620k; R_0402_1005Metric
SW3: SW_Push; SW_Push_SPST_NO_Alps_SKRK
U9: X096-2864TMBAG01-H30

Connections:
/Inner Buck Converter 4V/4V_{CC}: Q1.2, R42.1; also elsewhere on the board
/MCU/3.3V_{CC}: C47.1, C48.1, R18.1, U9.9 (VDD), U9.11 (BS1); also elsewhere on the board
/MCU/GPIO15: Q4.1, R44.1; also elsewhere on the board
/MCU/SCL: U9.18 (D0); also elsewhere on the board
/MCU/SDA: U9.19 (D1), U9.20 (D2); also elsewhere on the board
/OLED Display/RES#: R18.2, SW3.1, U9.14 (RES#)
/OLED Display/V_{BAT}: Q1.3, U9.6 (VBAT)
GND: C47.2, C48.2, C49.1, C50.1, Q4.2, R43.1, R44.2, SW3.2, U9.1 (N.C.(GND)), U9.8 (VSS), U9.10 (BS0), U9.12 (BS2), U9.13 (CS#), U9.15 (D/C#), U9.16 (R/W#), U9.17 (E/RD#), U9.21 (D3), U9.22 (D4), U9.23 (D5), U9.24 (D6), U9.25 (D7), U9.29 (VLSS), U9.30 (N.C.(GND)); also elsewhere on the board
unnamed: Q1.1, Q4.3, R42.2
unnamed: C52.2, U9.5 (C1N)
unnamed: C52.1, U9.4 (C1P)
unnamed: C51.2, U9.3 (C2N)
unnamed: C51.1, U9.2 (C2P)
unnamed: R43.2, U9.26 (IREF)
unnamed: C50.2, U9.28 (VCC)
unnamed: C49.2, U9.27 (VCOMH)

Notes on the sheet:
RES#
Electronic Swtich Circuit
Main Display
